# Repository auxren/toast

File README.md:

2HP passive TiniJax to euro conversion

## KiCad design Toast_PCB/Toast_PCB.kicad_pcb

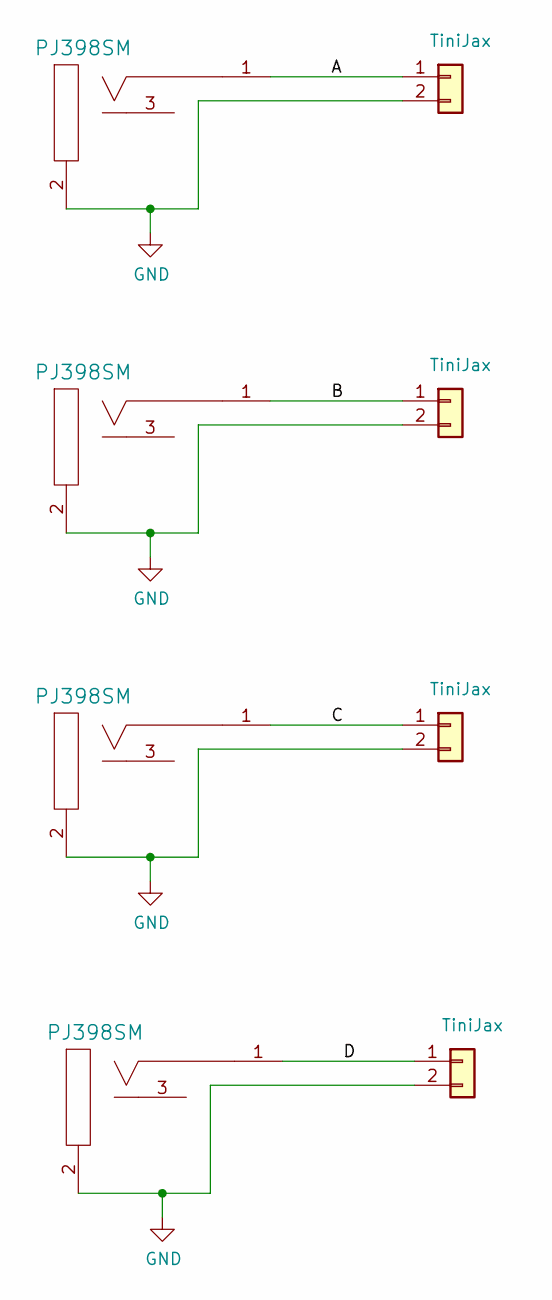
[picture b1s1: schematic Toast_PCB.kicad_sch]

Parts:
J1, J2, J4, J7: 3.5mm_Mono_Switched; EighthInch_PJ398SM; Part Number WQP-WQP518MA
J3, J5, J6, J8: TiniJax; Switchcraft_41; Part Number 1-0201FBV0T

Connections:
/A: J1.1 (SIG), J5.1
/B: J2.1 (SIG), J3.1
/C: J4.1 (SIG), J6.1
/D: J7.1 (SIG), J8.1
GND: J1.2 (SHEILD), J2.2 (SHEILD), J3.2, J4.2 (SHEILD), J5.2, J6.2, J7.2 (SHEILD), J8.2

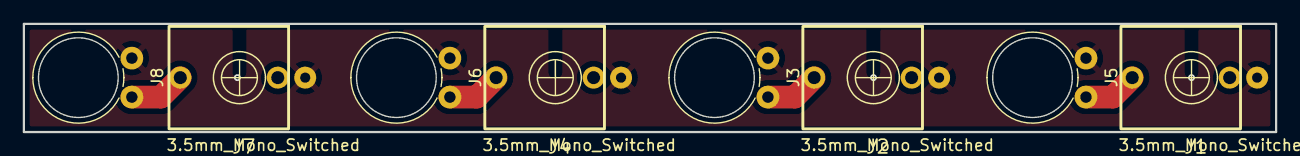
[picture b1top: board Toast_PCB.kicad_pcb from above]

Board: 2 copper layers, 110.0 x 9.5 mm, 8 parts (0 on the bottom side), 5 nets.

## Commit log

2024-05-29 DesignCommitV0.1
